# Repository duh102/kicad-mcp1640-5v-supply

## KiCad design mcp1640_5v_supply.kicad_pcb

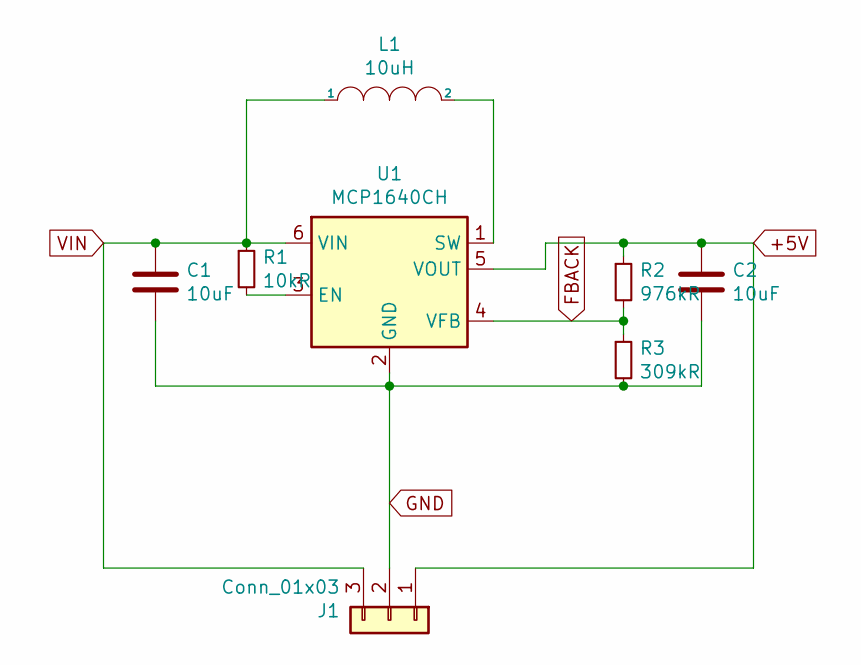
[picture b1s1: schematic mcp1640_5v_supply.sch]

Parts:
C1, C2: 10uF; C_0805_2012Metric
J1: Conn_01x03; PinHeader_1x03_P2.54mm_Vertical
L1: 10uH; L_Taiyo-Yuden_NR-50xx
R1: 10kR; R_0805_2012Metric
R2: 976kR; R_0805_2012Metric
R3: 309kR; R_0805_2012Metric
U1: MCP1640CH; SOT-23-6

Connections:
+5V: C2.1, J1.1, R2.1, U1.5 (VOUT)
FBACK: R2.2, R3.1, U1.4 (VFB)
GND: C1.2, C2.2, J1.2, R3.2, U1.2 (GND)
unnamed: L1.2, U1.1 (SW)
unnamed: R1.2, U1.3 (EN)
VIN: C1.1, J1.3, L1.1, R1.1, U1.6 (VIN)

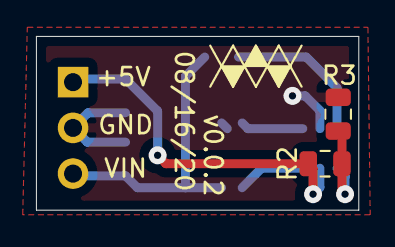
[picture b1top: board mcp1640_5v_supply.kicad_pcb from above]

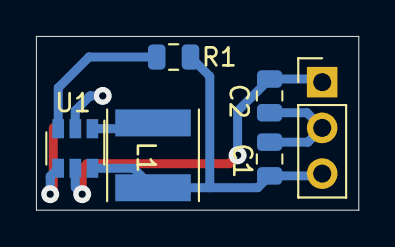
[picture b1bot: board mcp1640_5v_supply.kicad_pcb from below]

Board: 2 copper layers, 17.9 x 9.7 mm, 8 parts (6 on the bottom side), 6 nets.

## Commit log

2020-04-10 Finished module (probably)
2020-12-09 Another revision
